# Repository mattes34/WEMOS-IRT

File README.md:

# WEMOS-IRT

This is only for testing. Maybe many things are not correct. Use of one risk

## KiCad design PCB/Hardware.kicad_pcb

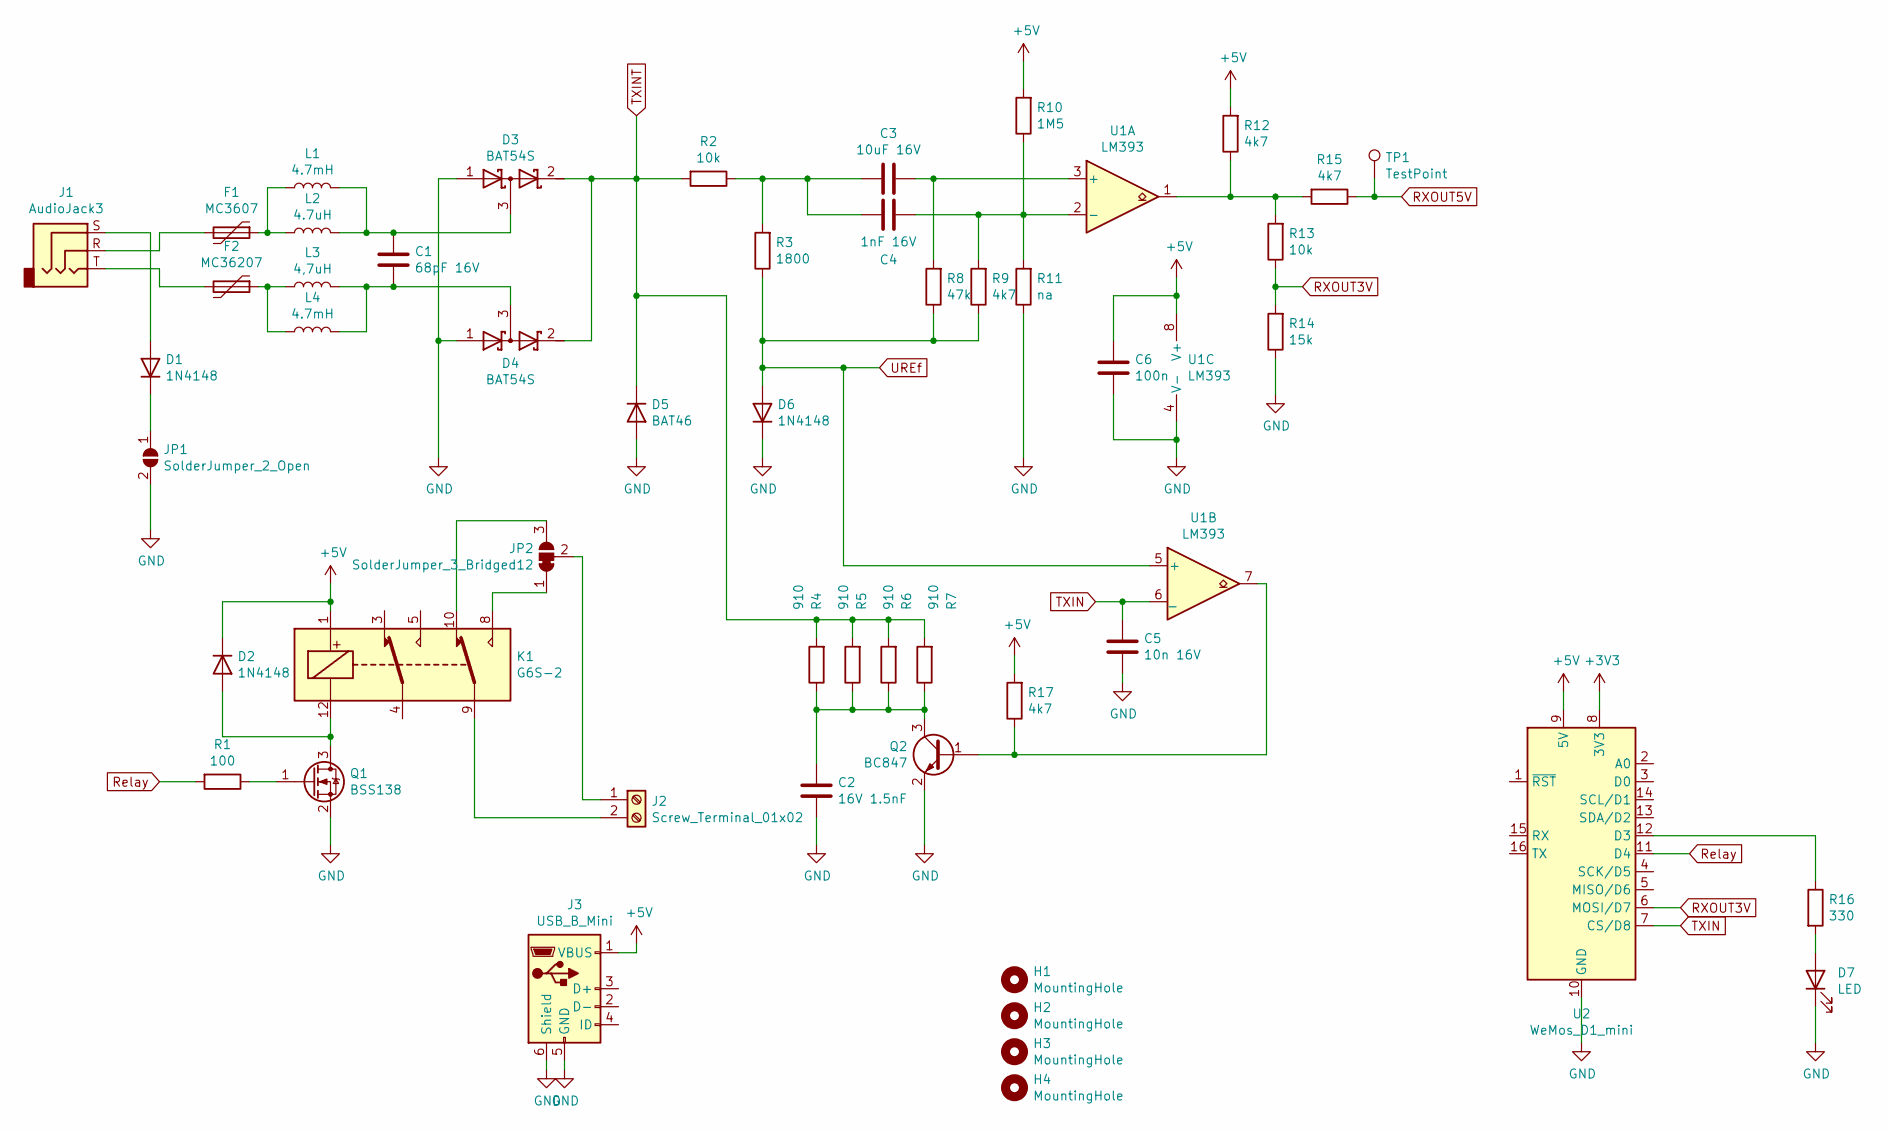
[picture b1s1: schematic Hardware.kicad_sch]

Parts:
C1: 68pF 16V; C_0805_2012Metric_Pad1.18x1.45mm_HandSolder
C2: 16V 1.5nF; C_0805_2012Metric_Pad1.18x1.45mm_HandSolder
C3: 10uF 16V; C_0805_2012Metric_Pad1.18x1.45mm_HandSolder
C4: 1nF 16V; C_0805_2012Metric_Pad1.18x1.45mm_HandSolder
C5: 10n 16V; C_0805_2012Metric_Pad1.18x1.45mm_HandSolder
C6: 100n; C_0805_2012Metric_Pad1.18x1.45mm_HandSolder
D1, D2, D6: 1N4148; D_MiniMELF
D3, D4: BAT54S; SOT-23
D5: BAT46; D_SOD-123
D7: LED; LED_0805_2012Metric_Pad1.15x1.40mm_HandSolder
F1: MC3607; R_1206_3216Metric_Pad1.30x1.75mm_HandSolder
F2: MC36207; R_1206_3216Metric_Pad1.30x1.75mm_HandSolder
H1, H2, H3, H4: MountingHole; MountingHole_2.2mm_M2
J1: AudioJack3; Jack_3.5mm_CUI_SJ-3523-SMT_Horizontal
J2: Screw_Terminal_01x02; TerminalBlock_Phoenix_MKDS-3-2-5.08_1x02_P5.08mm_Horizontal
J3: USB_B_Mini; USB_Mini-B_Wuerth_65100516121_Horizontal
JP1: SolderJumper_2_Open; SolderJumper-2_P1.3mm_Open_RoundedPad1.0x1.5mm
JP2: SolderJumper_3_Bridged12; SolderJumper-3_P1.3mm_Open_RoundedPad1.0x1.5mm
K1: G6S-2; Relay_DPDT_Omron_G6S-2
L1, L4: 4.7mH; L_Axial_L12.8mm_D5.8mm_P5.08mm_Vertical_Fastron_HBCC
L2: 4.7uH; L_1206_3216Metric_Pad1.22x1.90mm_HandSolder
L3: 4,7uH; L_1206_3216Metric_Pad1.22x1.90mm_HandSolder
Q1: BSS138; SOT-23
Q2: BC847; SOT-23
R1: 100; R_0805_2012Metric_Pad1.20x1.40mm_HandSolder
R2, R13: 10k; R_0805_2012Metric_Pad1.20x1.40mm_HandSolder
R3: 1800; R_0805_2012Metric_Pad1.20x1.40mm_HandSolder
R4, R5, R6, R7: 910; R_0805_2012Metric_Pad1.20x1.40mm_HandSolder
R8: 47k; R_0805_2012Metric_Pad1.20x1.40mm_HandSolder
R9, R12, R15, R17: 4k7; R_0805_2012Metric_Pad1.20x1.40mm_HandSolder
R10: 1M5; R_0805_2012Metric_Pad1.20x1.40mm_HandSolder
R11: na; R_0805_2012Metric_Pad1.20x1.40mm_HandSolder
R14: 15k; R_0805_2012Metric_Pad1.20x1.40mm_HandSolder
R16: 330; R_0805_2012Metric_Pad1.20x1.40mm_HandSolder
TP1: TestPoint; TestPoint_Pad_D1.0mm
U1: LM393; SOIC-8_3.9x4.9mm_P1.27mm
U2: WeMos_D1_mini; WEMOS_D1_mini_light

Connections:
+3V3: U2.8 (3V3)
+5V: C6.1, D2.1 (K), J3.1 (VBUS), K1.1, R10.2, R12.2, R17.2, U1.8 (V+), U2.9 (5V)
GND: C2.2, C5.2, C6.2, D3.1 (A), D4.1 (A), D5.2 (A), D6.1 (K), D7.1 (K), J3.5 (GND), J3.6 (Shield), JP1.2 (B), Q1.2 (S), Q2.2 (E), R11.1, R14.1, U1.4 (V-), U2.10 (GND)
unnamed: C1.1, D3.3 (common), L1.2, L2.2
unnamed: C1.2, D4.3 (common), L3.2, L4.2
unnamed: C2.1, Q2.3 (C), R4.1, R5.1, R6.1, R7.1
unnamed: C3.1, R8.2, U1.3 (+)
unnamed: C3.2, C4.1, R2.1, R3.2
unnamed: C4.2, R9.2, R10.1, R11.2, U1.2 (-)
unnamed: D1.1 (K), JP1.1 (A)
unnamed: D1.2 (A), J1.S
unnamed: D2.2 (A), K1.12, Q1.3 (D)
unnamed: D7.2 (A), R16.2
unnamed: F1.1, L1.1, L2.1
unnamed: F1.2, J1.R
unnamed: F2.1, L3.1, L4.1
unnamed: F2.2, J1.T
unnamed: J2.1, JP2.2 (C)
unnamed: J2.2, K1.9
unnamed: JP2.1 (A), K1.8
unnamed: JP2.3 (B), K1.10
unnamed: Q1.1 (G), R1.1
unnamed: Q2.1 (B), R17.1, U1.7
unnamed: R12.1, R13.2, R15.2, U1.1
unnamed: R16.1, U2.12 (D3)
RXOUT3V: R13.1, R14.2, U2.6 (MOSI/D7)
RXOUT5V: R15.1, TP1.1
Relay: R1.2, U2.11 (D4)
TXIN: C5.1, U1.6 (_), U2.7 (CS/D8)
TXINT: D3.2 (K), D4.2 (K), D5.1 (K), R2.2, R4.2, R5.2, R6.2, R7.2
UREf: D6.2 (A), R3.1, R8.1, R9.1, U1.5 (+)

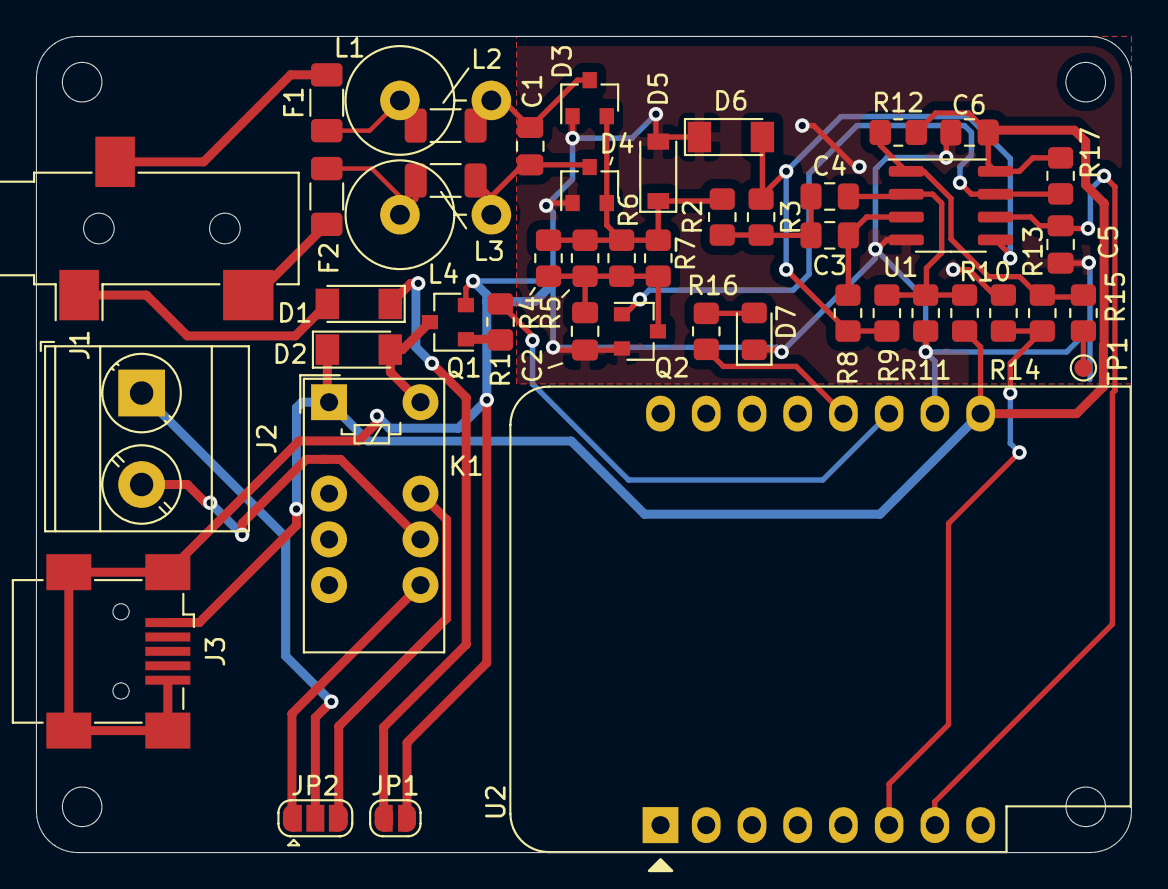
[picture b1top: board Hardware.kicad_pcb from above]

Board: 2 copper layers, 60.8 x 45.3 mm, 51 parts (0 on the bottom side), 30 nets.

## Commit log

2022-12-12 - first commit
2022-12-12 Update README.md
    update Readme
